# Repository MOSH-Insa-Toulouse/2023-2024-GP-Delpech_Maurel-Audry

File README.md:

# Projet-MOSH-INSA-Toulouse-2023-2024-Capteur-Graphite
## Implémentation d'un capteur de déformation/jauge de contrainte à base de graphite issu de crayons à papier HB à 2H.
Les jauges de contraintes sont des capteurs résistifs permettant de quantifier la déformation appliquée sur une structure. Ces capteurs sont souvent utilisés dans l'industrie car ils sont peu coûteux et facile à mettre en place. (Pencil Drawn Strain Gauges and Chemiresistors on Paper Cheng-Wei Lin, Zhibo Zhao, Jaemyung Kim & Jiaxing Huang Department of Materials Science and Engineering, Northwestern University 2220 Campus Drive, Evanston, IL, 60208, USA).
La mesure de résistance de ce type de crayon nécessite une amplification nous avons donc créé un Shield Arduino pour le traitement du signal et son affichage.

## Livrables
- Un shield arduino permettant le conditionnement des mesures du capteur graphite, leur traitement et leur affichage.
- Une code arduino permettant le choix du gain de l'amplificateur, la communication en bleutooth via un module HC 05 et l'affichage des mesure sur un écran OLED.
- Une datasheet du capteur de contrainte low-tech

## Hardware utilisé
- 1 carte Arduino Uno
- 1 Module Bluetooth HC-05
- 1 Encodeur rotatoire
- 1 Écran OLED01
- 1 Flex sensor
- 1 Potentiomètre digital MCP-41050
- 1 AOP LTC1050

# Simulation du circuit amplificateur sur LTspice
Un circuit de transimpédance est utilisé pour elever le faible signal du capteur (100nA) à un signal lisible pour le microcontroleur de l'Arduino.

Différents étages de filtres passes-bas permettent de couper les hautes fréquences et le 50 Hz et ainsi diminuer le bruit sur la mesure.
  - Fréquence de coupure de l'étage 1 : 16 Hz
  - Fréquence de coupure de l'étage 2 : 1.6 Hz
  - Fréquence de coupure de l'étage 3 : 1.6 kHz

La simulation permet de verifier qu'à 50 Hz le signal est atténué de -40 dB, le bruit du secteur seras alors grandement diminié et ne perturberas pas la mesure. 

# Design du PCB sur KiCAD et fabrication du shield

Le PCB inclu l'amplificateur de transimpédance et différents modules permettant l'affichage ou le traitment des données. En partant d’un template d’une carte Arduino Uno, il a fallu :
  - Reproduire la schématique du circuit transimpédance et créer de nouveaux symboles pour les modules spécifiques à notre projet.
  - Concevoir les empreintes réelles de ces modules en prenant en compte leurs caractéristiques physiques (nombres de pins, distance entre les pins, géométrie des empreintes…)
  - Effectuer le routage du circuit à partir du chevelu
  - Poser le plan de masse pour référencer les pistes au GND

## Schema et empreintes des modules

Module Bluetooth HC 05 : ce module permet la communication des données vers une application androide. L'implemantation d'un échange entre une application et le microcontrolleur permet le stockage de donnée que l'arduino ne permettrais pas. Il permet aussi d'avoir une vue d'ensemble sur les mesures que le petit écran ne permttrais pas.

L'écran OLED : permet l'affichage des mesures et la selection du gain de l'amplificateur.

L'encodeur rotatoire : permet la navigation dans les menus. Le debouncing de l'encodeur a été réalisé en ajoutant des capacités sur les pins.

L'amplificateur de transimpédance avec le capteur graphite.

La résistance variable digitale MCP41050 : elle permet de changer la résistance R2 de l'amplificateur pour changer le gain.

## Schema du PCB complet

## Fabrication du shield

Le shield est réalisé sur des plaques d'époxy recouvertes d'une couche de cuivre. Une résine photosensible est appliquée sur la plaque avec par dessus, le calque du circuit. Le tout est ensuit placé sous lumière UV pour faire polymeriser la résine au endroits non protégé par le calque. La plque d'époxy est ensuite plongé dans du perchlorure de fer pour retirer la couche de cuivre qui n'est pas protégé par la résine, faisant ainsi apparaître les circuits.

L'étape suivante est de percer les trous pour faire passer les pins de la carte et les composants. Une fois les trous percés, on soude les composants et les headers à la plaque.

# Code Arduino
Le code a été réalisé sous Arduino IDE 2.3.2 et il est consultable 
[ici](https://github.com/MOSH-Insa-Toulouse/2023-2024-GP-Delpech_Maurel-Audry/tree/main/Master_code_projet_capteur).

On utilise la bibliothèque Adafruit_SSD1306 pour gérer l'écran OLED sur lequel on affiche deux sous-menus.
Le premier permet d'afficher la tension après amplification du capteur graphite, la conversion de cette tension en une valeur de résistance et enfin la résistance du capteur de flexion. Le second permet de moduler la résistance du MCP_41050.
Pour naviguer entre les menus et moduler cette résistance, on utilise l'encodeur rotatoire et on clique sur le bouton pour valider ou revenir au menu précédent. 
Les mesures sont ensuite transférées à l'application Android via le module bluetooth. 

# Application android

Le petit écran OLED ne permet pas d'afficher un graph et la petite mémoire de l'arduino ne permet pas de conserver les mesures. Le rôle de l'application android est de pouvoir faciliter l'affichage et le stockage des valeures de déformation.
Pour utiliser l'appliication il faut, dans un premier temps, appairer le telephone au module Bleutooth grâce au menu déroulant de l'app (ne pas oublier d'autoriser l'application à utiliser le bluetooth).
Si le télephone est connecté, l'application recevras les données en continu et les reporteras sur le graphique déroulant. En parrallèle, l'application envoi aussi toutes les mesures sur une page google sheets pour le stockage.

# Banc de test

Comme banc de test, nous avons utilisé 7 demi cylindres de différents diamètres allant de 2 à 5 cm avec un pas de 0,5 cm. La géométrie des cylindres est connue, il est possbile de remonter à la défromation avec la formule suivante :

$$\epsilon = \frac{e}{2r}$$ 
 
avec e l’épaisseur du capteur et r le rayon de courbure. Les mesures sont réalisées en tension.

2 des différents capteurs utilisés :

Suite aux mesures de résistance nous obtenons les courbes suivantes.
Pour l'extension :

Pour la compression :

# Datasheet
La fiche technique est consultable [ici](datasheet.pdf).

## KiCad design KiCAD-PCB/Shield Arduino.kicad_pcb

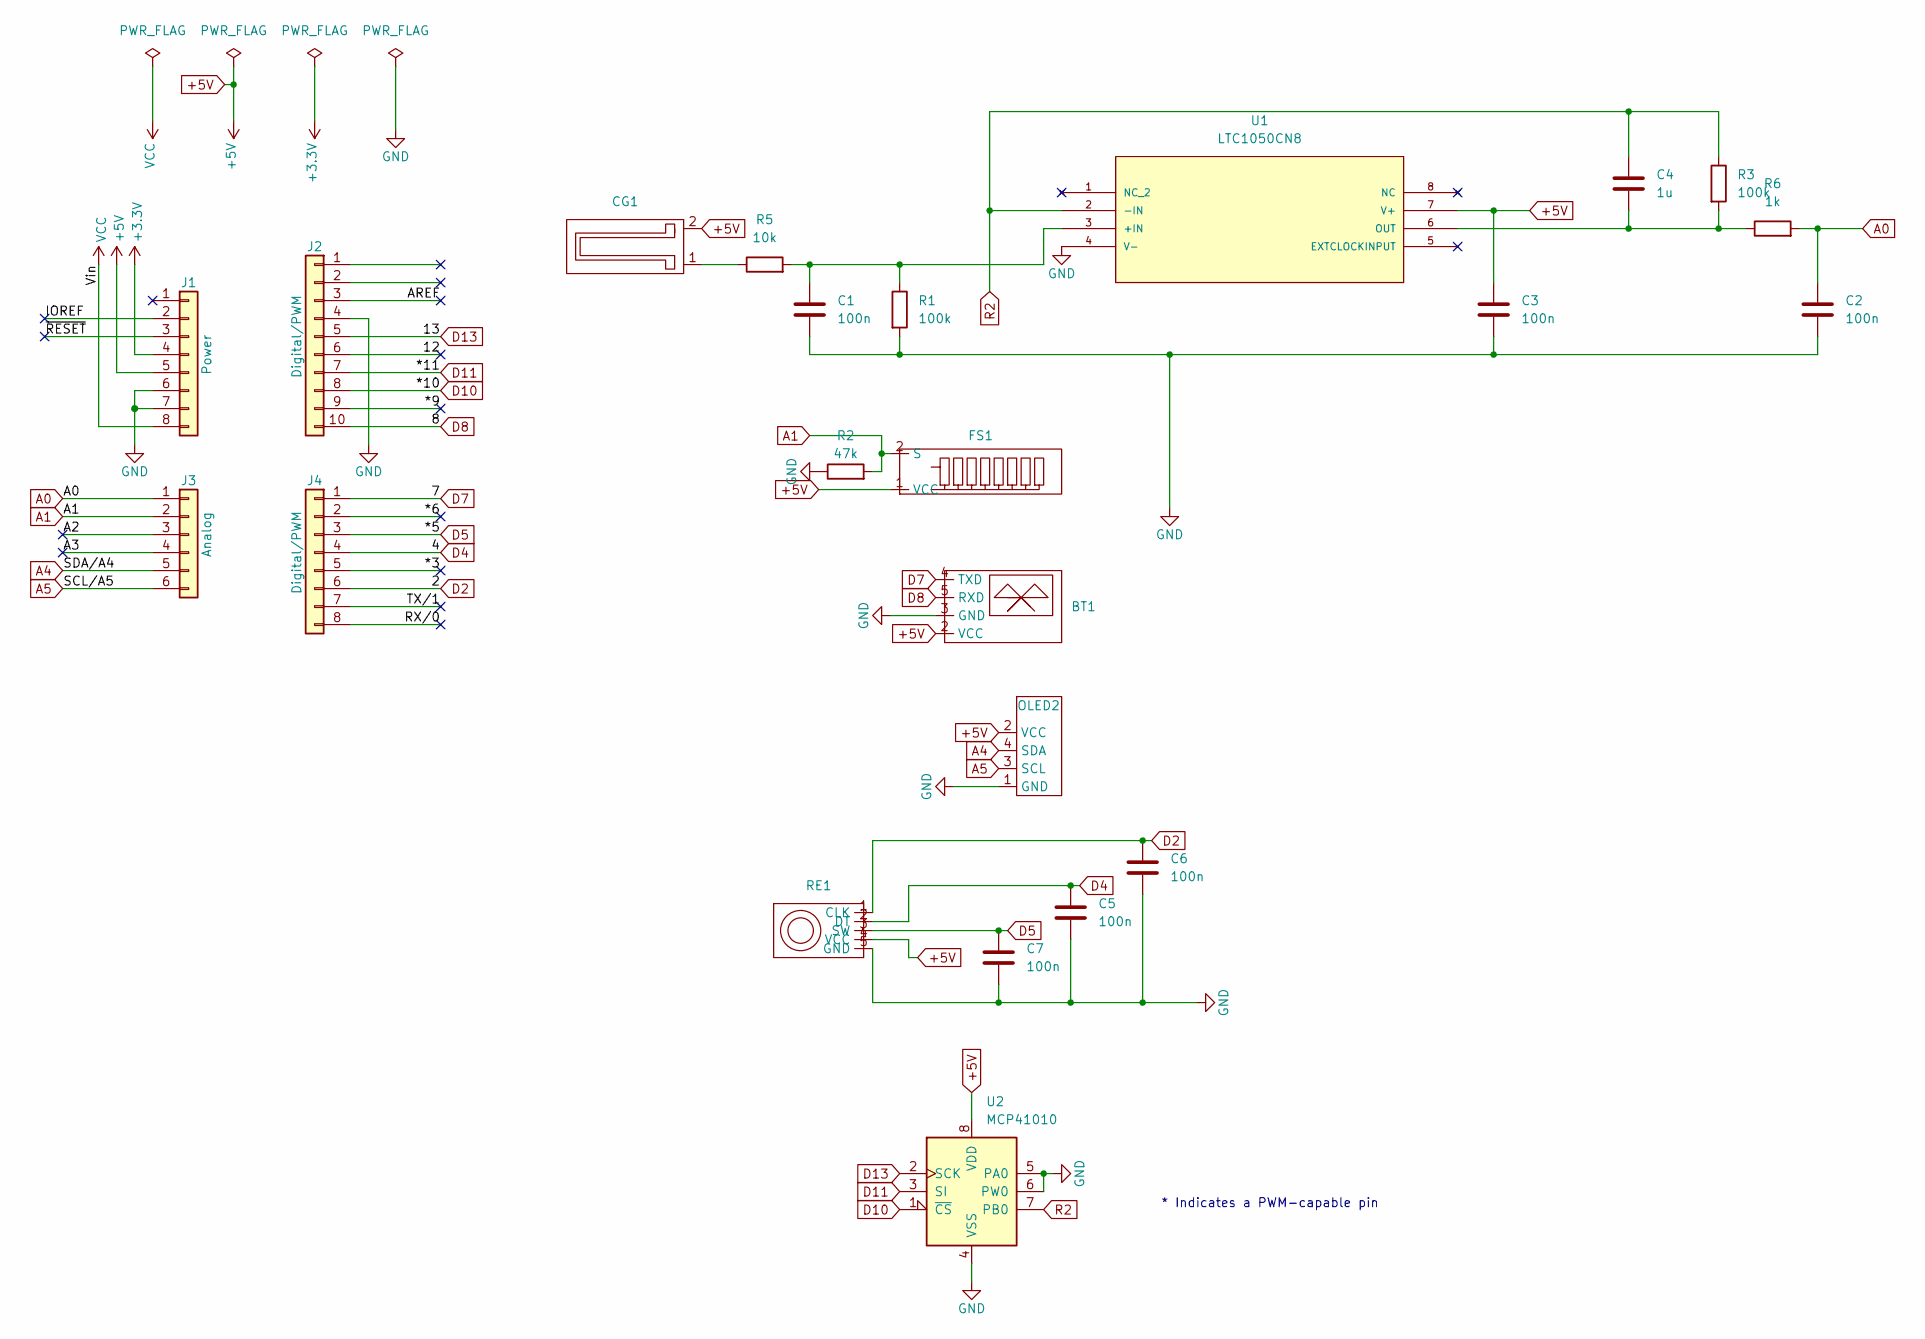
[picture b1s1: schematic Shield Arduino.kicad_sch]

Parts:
BT1: PinSocket_1x06_P2.54mm_Vertical
C1, C2, C3, C5, C6, C7: 100n; C_Disc_D4.3mm_W1.9mm_P5.00mm
C4: 1u; C_Rect_L7.0mm_W4.5mm_P5.00mm
CG1: PinSocket_1x02_P2.54mm_Vertical
FS1: PinSocket_1x02_P2.54mm_Vertical
J1: Power; PinSocket_1x08_P2.54mm_Vertical
J2: Digital/PWM; PinSocket_1x10_P2.54mm_Vertical
J3: Analog; PinSocket_1x06_P2.54mm_Vertical
J4: Digital/PWM; PinSocket_1x08_P2.54mm_Vertical
OLED2: PinSocket_1x04_P2.54mm_Vertical
R1, R3: 100k; R_Axial_DIN0207_L6.3mm_D2.5mm_P10.16mm_Horizontal
R2: 47k; R_Axial_DIN0207_L6.3mm_D2.5mm_P10.16mm_Horizontal
R5: 10k; R_Axial_DIN0207_L6.3mm_D2.5mm_P10.16mm_Horizontal
R6: 1k; R_Axial_DIN0207_L6.3mm_D2.5mm_P10.16mm_Horizontal
RE1: PinSocket_1x05_P2.54mm_Vertical
U1: LTC1050CN8; DIP-8_W7.62mm
U2: MCP41010; DIP-8_W7.62mm

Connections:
+3V3: J1.4
+5V: BT1.2 (VCC), C3.2, CG1.2, FS1.1 (VCC), J1.5, OLED2.2 (VCC), RE1.4 (VCC), U1.7 (V+), U2.8 (VDD)
/12: J2.6
/*3: J4.5
/*6: J4.2
/*9: J2.9
/A2: J3.3
/A3: J3.4
/AREF: J2.3
/IOREF: J1.2
/RX/0: J4.8
/TX/1: J4.7
/~RESET: J1.3
A0: C2.1, J3.1, R6.2
A1: FS1.2 (S), J3.2, R2.2
A4: J3.5, OLED2.4 (SDA)
A5: J3.6, OLED2.3 (SCL)
D2: C6.1, J4.6, RE1.1 (CLK)
D4: C5.1, J4.4, RE1.2 (DT)
D5: C7.1, J4.3, RE1.3 (SW)
D7: BT1.4 (TXD), J4.1
D8: BT1.5 (RXD), J2.10
D10: J2.8, U2.1 (~CS)
D11: J2.7, U2.3 (SI)
D13: J2.5, U2.2 (SCK)
GND: BT1.3 (GND), C1.2, C2.2, C3.1, C5.2, C6.2, C7.2, J1.6, J1.7, J2.4, OLED2.1 (GND), R1.2, R2.1, RE1.5 (GND), U1.4 (V-), U2.4 (VSS), U2.5 (PA0), U2.6 (PW0)
unnamed: CG1.1, R5.1
unnamed: C1.1, R1.1, R5.2, U1.3 (+IN)
unnamed: C4.1, R3.2, R6.1, U1.6 (OUT)
R2: C4.2, R3.1, U1.2 (-IN), U2.7 (PB0)
VCC: J1.8

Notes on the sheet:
* Indicates a PWM-capable pin

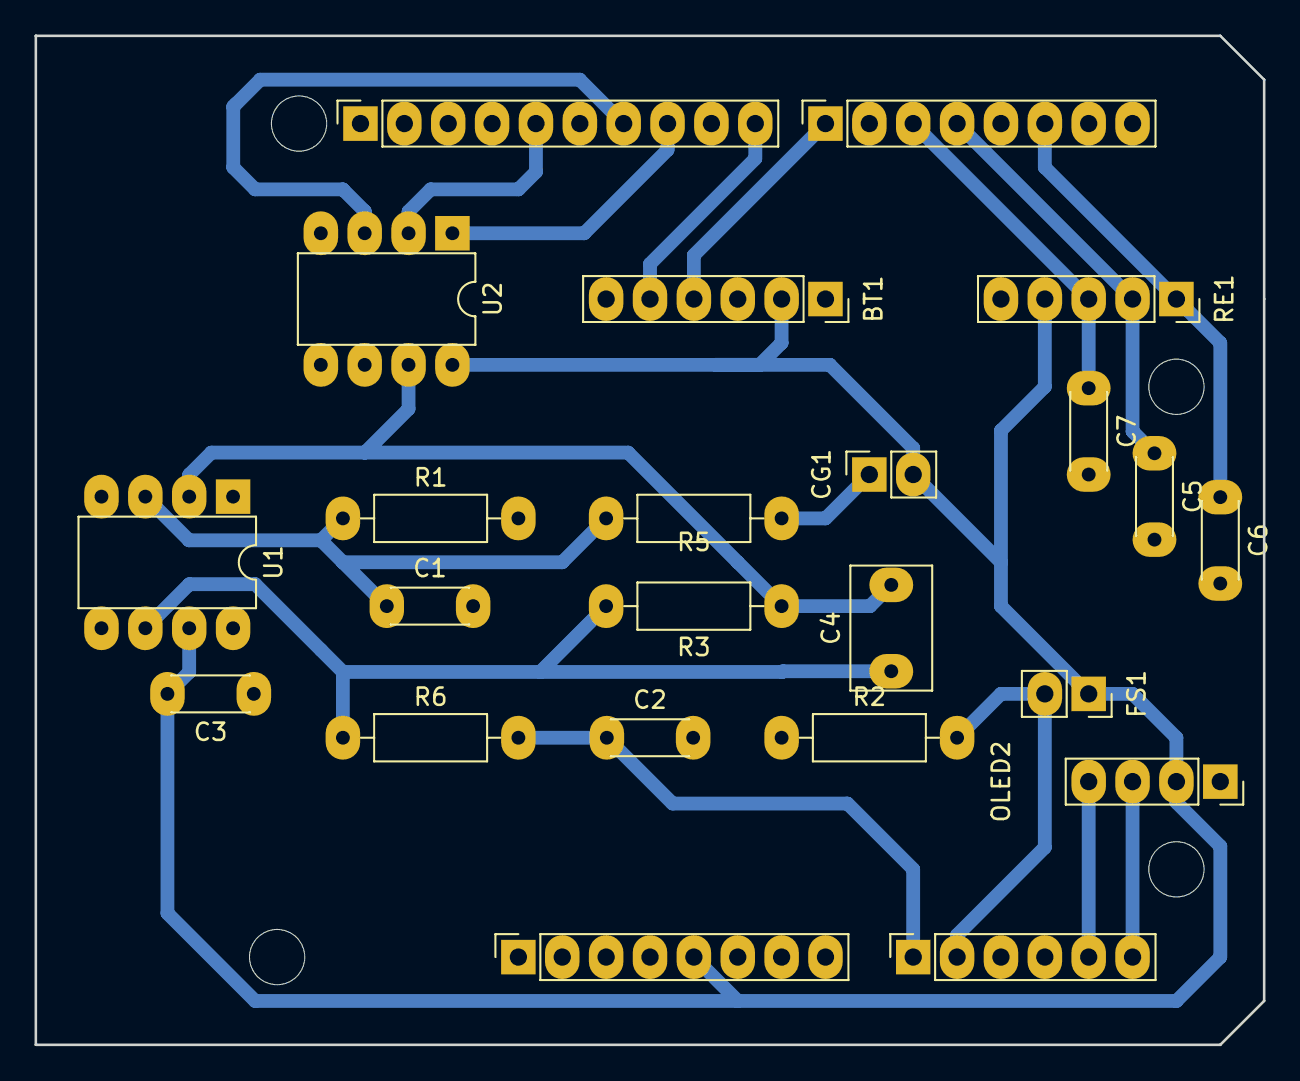
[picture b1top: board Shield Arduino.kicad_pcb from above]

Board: 2 copper layers, 71.1 x 58.4 mm, 27 parts (0 on the bottom side), 18 nets.

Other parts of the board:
MH1, MH2, MH3, MH4: MountingHole_3.2mm

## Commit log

2024-05-30 Create Application Android
